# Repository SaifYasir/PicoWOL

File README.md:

# PicoWOL

Rasberry Pi Pico to send WOL packets

This project provides both physical and remote means to wake up machines configured with wake-on-lan.

## Documentation
To generate documentation Doxygen must be installed, simply call doxygen in the root folder of this project and doxygen documentation will be generated.

## Third Party Dependencies
This project relies on [carlk3's](https://github.com/carlk3/no-OS-FatFS-SD-SPI-RPi-Pico) great work in creating an sd card library for the Rasberry Pi Pico.

## Aquiring Hardware
To see how to aquire required hardware see [readme](pcb_board/README.md).

## Usage

This program allows the picowol to turn machines on through [Wake-on-lan](https://en.wikipedia.org/wiki/Wake-on-LAN). Pico_WOL can either turn machines by using physical buttons on the device or sending a UDP packet (see ...) to the microcontroller's ip to turn the requested device on. The precompiled uf2 file sets External components to certain GPIO pins on the pico, these will be listed in case you wish not to buy a pcb.

- [Physical Buttons](#physical-buttons)
- [Micro SD Card Reader](#micro-sd-card-reader)
- [Display](#display)

### Physical Buttons

The list below provides detail of what each button does and the mappings via GPIO to the Rasberry Pi Pico.

1. Allows the User to cycle between profiles, moving left. - GPIO 14
2. Provides basic information about the wireless pico, IP Address and the port in use (If you want to send packets to server) - GPIO 19
3. Allows the User to cycle between profiles, moving right. - GPIO 15
4. Wakes the selected profile. - GPIO 18

### Micro SD Card Reader

This reader is responsible in loading profiles and getting neccessary details to connect to the network.

#### Reading WiFi credentails

This program expects the file 'wifi_credentials.txt' to be at the base of the SD card in which will store the required credentials.
The credentials are seperated via semi colons and in the structure: SSID;SSID_PASSWORD i.e. VM112121;password123

#### Reading Wake On Lan Profiles

This program currently expects all profiles to be loaded in a singular file called 'wol_profiles.txt' which stores the name of the profile and its respective IP Address. 
The structure of storing profiles is as so: PROFILE_NAME;MACADDRESS ie gaming_pc;60ABDBA2A2A8.

Such that the file looks like this:

- Profile1;60ABDBA2A2A8
- Profile2;60ABDBA2A2A9
- Profile3;60ABDBA2A2AA

#### GPIO Connections

- SPI Chip Select - GPIO 13
- SPI RX - GPIO 12
- SPI TX - GPIO 11
- SPI SCK - GPIO 10

## Display

This display enables the user to view the currently selected profile.

The GPIO Mappings are as so:
- I2C_SDA - GPIO 16
- I2C_SCL - GPIO 17

## Potential future Improvements

This project was mainly a way for myself to learn more about microcontrollers and become more familiar with technologies like CMake and Doxygen.
However this program could do with a few improvements, mainly:

-   Wake on lan profile to be read across multiple files
-   Wake on lan profiles can be saved via UDP packets to Pico UDP server
-   Seperate Display from Pico Server, such that the server starts, even when the display is not initialised (working headless)

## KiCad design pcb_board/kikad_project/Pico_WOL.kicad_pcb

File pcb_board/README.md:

# Hardware aquirement
This readme covers gathering relevant parts for the final build

## KiKad Project

This contains directory components gathered from my KiKad project, this should allow anyone to either grab gerber files needed for print or regenerate the gerber files needed.

## Case

I've created a STL file to hold both the display and the provided PCB Board, [here](case/case.stl).

## Build Components

Below is a list of components used to build the project:

- [Rasberry pi pico wireless (soldered heads)](https://www.amazon.co.uk/DVOZVO-Raspberry-Pre-Soldered-Wireless-Connectivity/dp/B0BV1H4D7M/ref=sr_1_3?crid=38OD8XVM6FVOO&dib=eyJ2IjoiMSJ9.5rrltWqY9Rv3jpucgPGsIn_evCD9ElsqvSv3SyBkfBBdMS7BwKJBqI7jxlJDz_RYciQIycxvgjo9YFPT91diZXax1RgA821CUeKQQcpJ5ATvFS5mBq9dWzCbHII750q_0em2XcvZniiZofDEysHM3SiygeNd2Ke7NYam3Ru6180VWZFca0piPCD7Os2bQN3DHKl01l27eNVioleXR6OzugXnwsqrYtdG9qZ9_y3JrL4.f-zRNYZM28hRcX_Qza0ZqilIpFJtvcGUtWd_xj9ochU&dib_tag=se&keywords=raspberry+pi+pico+wireless&qid=1721581385&sprefix=rasberry+pi+pico+wirelss%2Caps%2C102&sr=8-3)

- [M3 screws](https://www.amazon.co.uk/dp/B08J3KY5RM?psc=1&ref=ppx_yo2ov_dt_b_product_details)

- [M3 screw threads](https://www.amazon.co.uk/dp/B0CYH466PM?psc=1&ref=ppx_yo2ov_dt_b_product_details)

- [5V charging board](https://www.amazon.co.uk/dp/B09NX3QDKF?psc=1&ref=ppx_yo2ov_dt_b_product_details)

- [Lithium battery](https://www.amazon.co.uk/dp/B08ZCQXFX4?psc=1&ref=ppx_yo2ov_dt_b_product_details)

- [Boost converter (3.7v to 5v)](https://www.amazon.co.uk/dp/B0C3QLH284?psc=1&ref=ppx_yo2ov_dt_b_product_details)

- [Micro SD Card reader](https://www.amazon.co.uk/dp/B09YYG6BT3?psc=1&ref=ppx_yo2ov_dt_b_product_details)

- [LCD Display (1602 I2C)](https://www.amazon.co.uk/dp/B09YYG6BT3?psc=1&ref=ppx_yo2ov_dt_b_product_details)

- [100u Capacitor (any would do really)](https://www.amazon.co.uk/s?k=100u+capacitor&crid=16SIGP58YYNJG&sprefix=100u+capacitor%2Caps%2C72&ref=nb_sb_noss)

- Wire (Im guessing you can source this yourself)

## Final Look
This is roughly what the final design would look like, ignore any jerry rigging of wires, this was due to my own created errors.

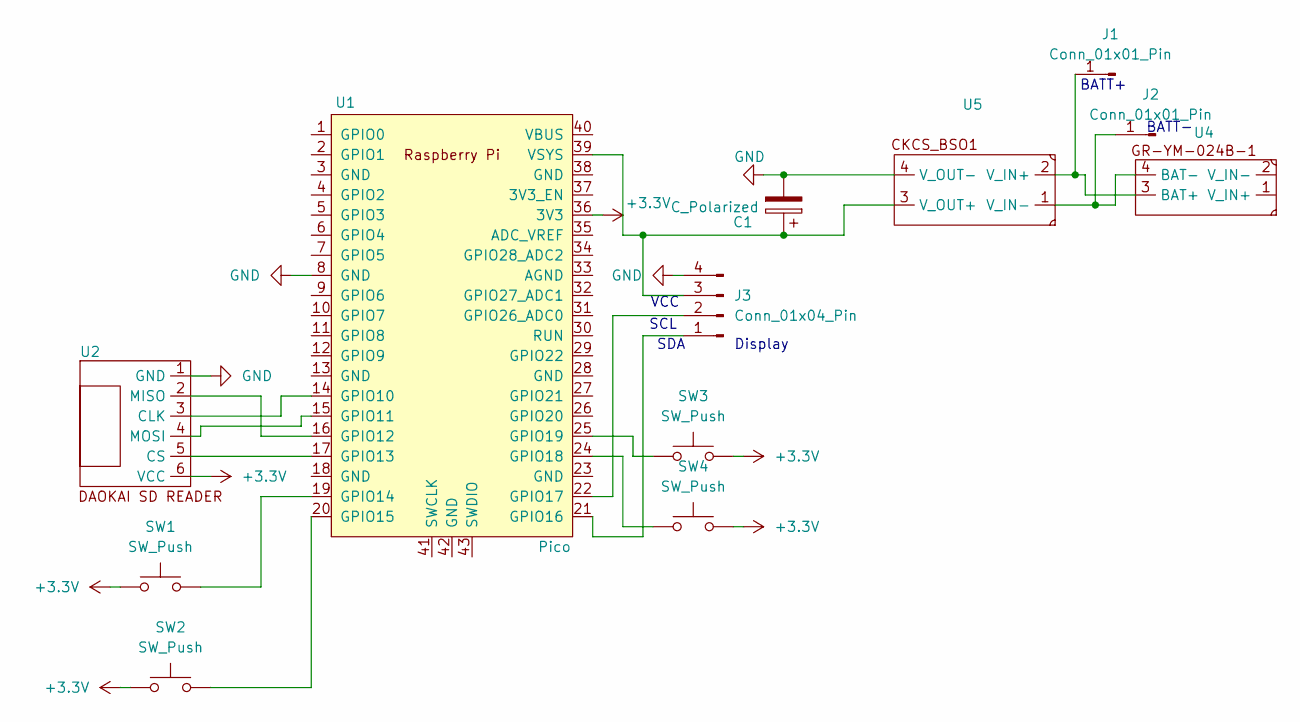
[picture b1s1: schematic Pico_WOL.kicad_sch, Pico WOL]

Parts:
C1: C_Polarized; CP_Radial_D5.0mm_P2.50mm
J1, J2: Conn_01x01_Pin; SolderWire-1.5sqmm_1x01_D1.7mm_OD3.9mm
J3: Conn_01x04_Pin; SolderWire-1.5sqmm_1x04_P7.8mm_D1.7mm_OD3.9mm
SW1, SW2, SW3, SW4: SW_Push; SW_PUSH_6mm
U1: Pico; RPi_Pico_SMD_TH
U2: Dokai_SD_READER
U4: USB_A_BATTERY_CHARGER
U5: boost_converter

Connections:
+3.3V: SW1.1, SW2.1, SW3.2, SW4.2, U1.36 (3V3), U2.6 (VCC)
GND: C1.2, J3.4, U1.8 (GND), U2.1 (GND), U5.4 (V_OUT-)
unnamed: J1.1, U4.3 (BAT+), U5.2 (V_IN+)
unnamed: J2.1, U4.4 (BAT-), U5.1 (V_IN-)
unnamed: J3.1, U1.21 (GPIO16)
unnamed: J3.2, U1.22 (GPIO17)
unnamed: C1.1, J3.3, U1.39 (VSYS), U5.3 (V_OUT+)
unnamed: U1.14 (GPIO10), U2.3 (CLK)
unnamed: U1.15 (GPIO11), U2.4 (MOSI)
unnamed: U1.16 (GPIO12), U2.2 (MISO)
unnamed: U1.17 (GPIO13), U2.5 (CS)
unnamed: SW1.2, U1.19 (GPIO14)
unnamed: SW2.2, U1.20 (GPIO15)
unnamed: SW4.1, U1.24 (GPIO18)
unnamed: SW3.1, U1.25 (GPIO19)

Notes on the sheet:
BATT-
SCL
VCC
Display
BATT+
SDA

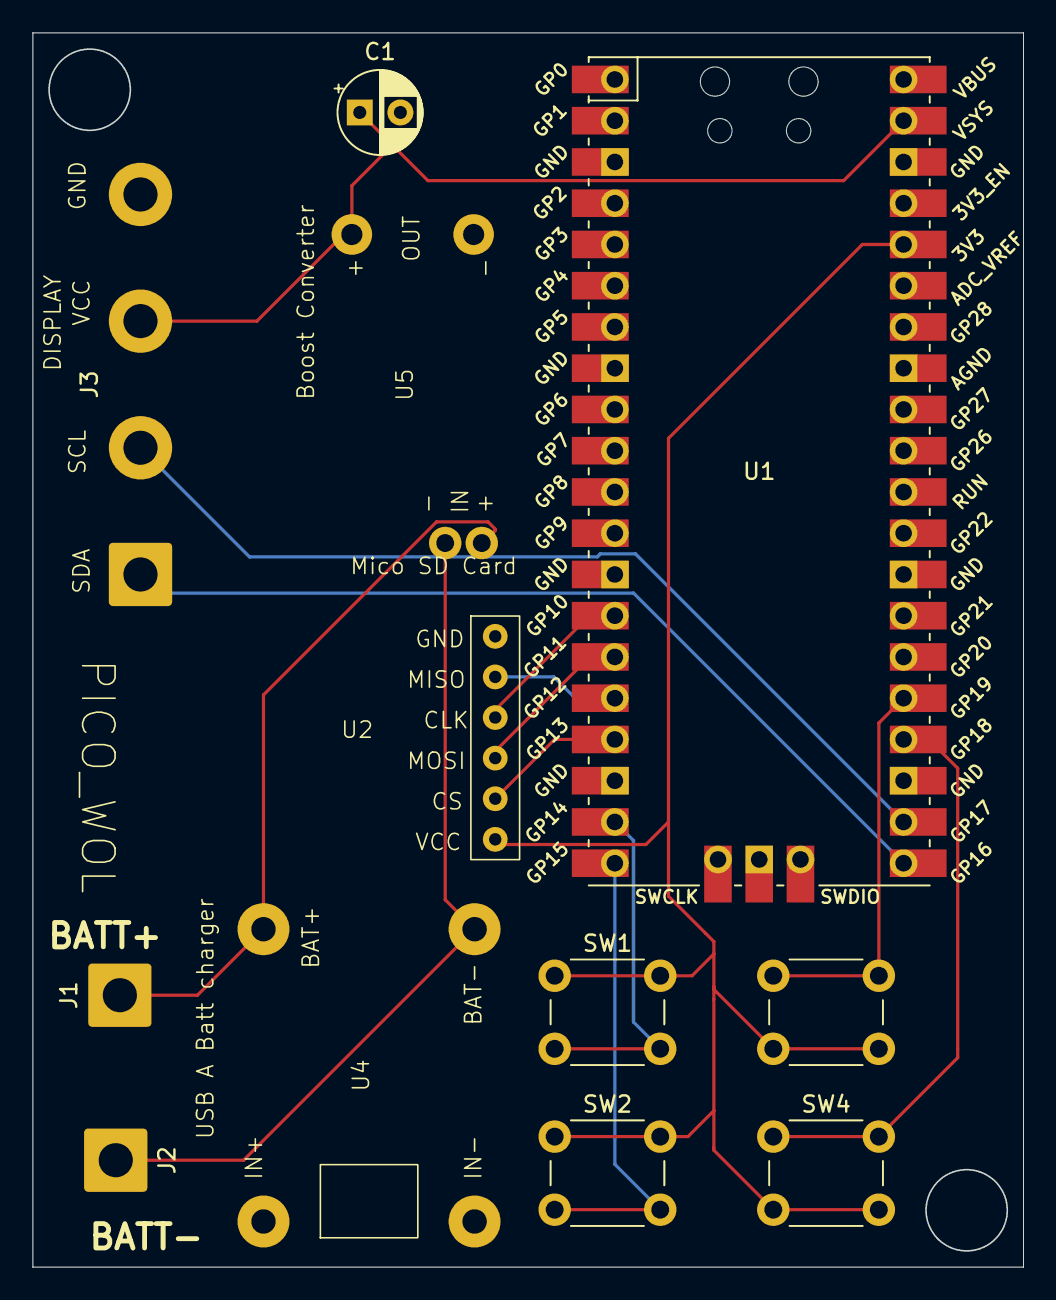
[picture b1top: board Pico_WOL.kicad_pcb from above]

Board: 2 copper layers, 61.0 x 76.0 mm, 12 parts (0 on the bottom side), 15 nets.

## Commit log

2023-12-22 added basic implementation to blink pico_w LED pin
2023-12-24 implementing WOL functionality
2023-12-25 added functionality for pico to interact with 16x2 display using I2C
2024-01-01 adding wol functionality to pico
2024-01-01 adding wol functionality
2024-01-03 adding functionality for buttons
2024-01-17 comments editied & implemented configuration file for SD cards
2024-01-22 Added configuration for SD cards (not yet implemented) aswell as adding additional functionality for WOL
2024-01-28 added accept button and functionality to wake up a device
2024-02-12 fixed commit issues
2024-02-14 working on implementation of sd card
2024-03-04 SD card now works and reads WOL profiles and WIFI credentials
2024-03-13 Moved UDP polling stack to a queue due to being threadsafe (therefore can be shared across both pico cores)
2024-03-16 Added additional functions ie getting ip to display
2024-03-20 Added rudimentary server functionality to pico
2024-03-23 Added additional functionality for server control
2024-03-25 Adding doxygen support
2024-03-26 Added commenting
2024-03-27 Added additional documentation
2024-03-31 Reverted using queues back to locally defined stacks, due to only using 1 core
2024-04-05 Added documentation
2024-04-14 Added additional feature to notify user when SD card cannot be read on display
2024-07-21 commented debug
2024-07-23 Added readmes and case/pcb files

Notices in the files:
pcb_board/kikad_project/Pico_WOL.kicad_sch:
MIT license
